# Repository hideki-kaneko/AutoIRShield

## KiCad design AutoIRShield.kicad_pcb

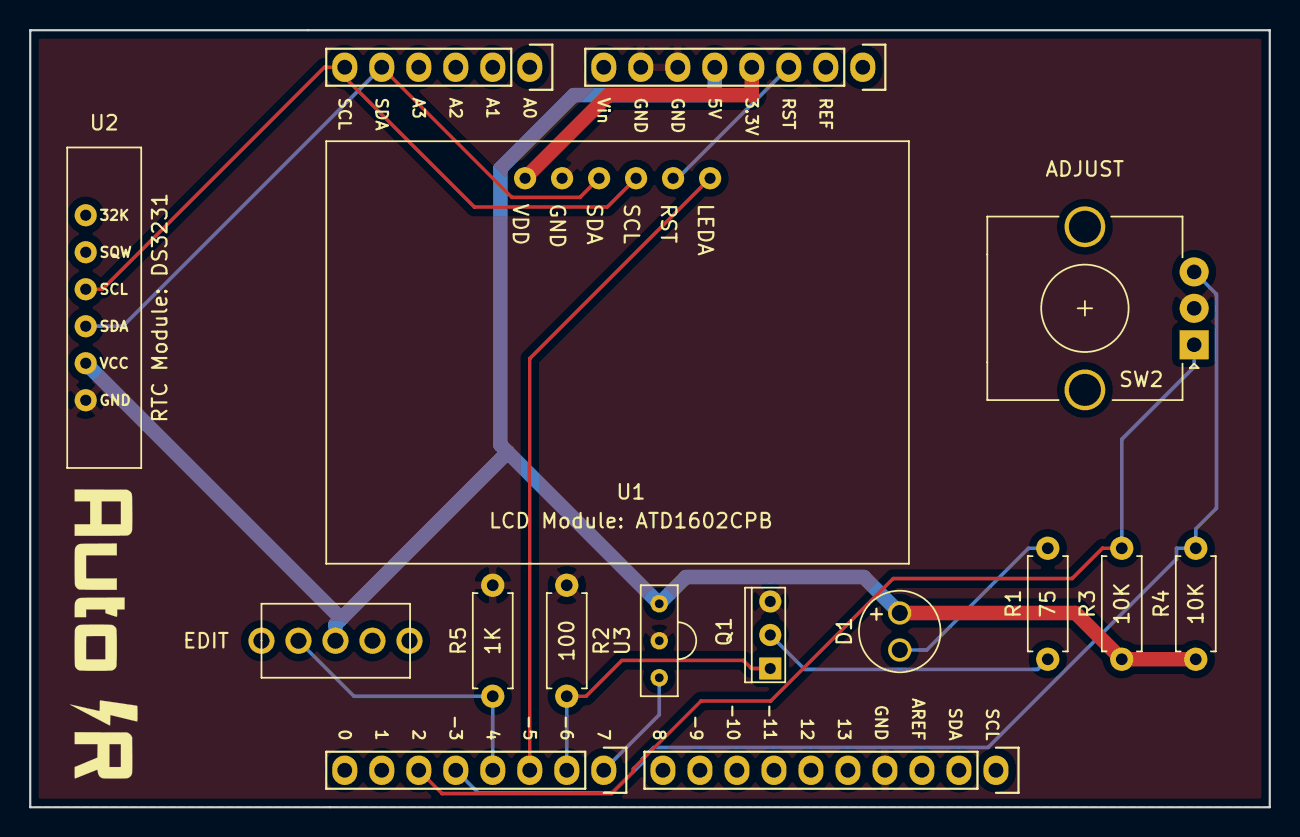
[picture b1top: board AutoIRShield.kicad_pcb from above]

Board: 2 copper layers, 85.1 x 53.3 mm, 16 parts (0 on the bottom side), 14 nets.

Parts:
D1: SID1k10CM; SID1K10CM
P1: Power; Socket_Strip_Arduino_1x08
P2: Analog; Socket_Strip_Arduino_1x06
P3: Digital; Socket_Strip_Arduino_1x10
P4: Digital; Socket_Strip_Arduino_1x08
Q1: 2SK4017
R1: 75; R_Axial_DIN0207_L6.3mm_D2.5mm_P7.62mm_Horizontal
R2: 100; R_Axial_DIN0207_L6.3mm_D2.5mm_P7.62mm_Horizontal
R3, R4: 10K; R_Axial_DIN0207_L6.3mm_D2.5mm_P7.62mm_Horizontal
R5: 1K; R_Axial_DIN0207_L6.3mm_D2.5mm_P7.62mm_Horizontal
SW1: 2MS1-T1-B4-VS2-Q-E-S; Switch_2MST1B4VS2QES
SW2: EC12E2420801
U1: ATD1602CPB
U2: RTC_DS3231; RTC_DS3231_Vertical
U3: IRReceiver_OSRB38C9AA

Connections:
+3V3: P1.4, U1.1
+5V: D1.2, P1.5, R3.1, R4.1, SW1.2, U2.2, U3.3
/2: P4.6, R3.2, SW2.A
/3(**): P4.5, R4.2, SW2.B
/4: P4.4, R5.1, SW1.1
/5(**): P4.3, U1.6
/6(**): P4.2, Q1.1, R2.2
/7: P4.1, U3.1
/A4(SDA): P2.5, U1.3, U2.3
/A5(SCL): P2.6, U1.4, U2.4
/Reset: P1.3, U1.5
GND: P1.6, P1.7, P3.4, Q1.3, R2.1, R5.2, SW2.C, U1.2, U2.1, U3.2
unnamed: D1.1, R1.2
unnamed: Q1.2, R1.1

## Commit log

2020-07-22 電源ラインの幅を太くして自動配線
